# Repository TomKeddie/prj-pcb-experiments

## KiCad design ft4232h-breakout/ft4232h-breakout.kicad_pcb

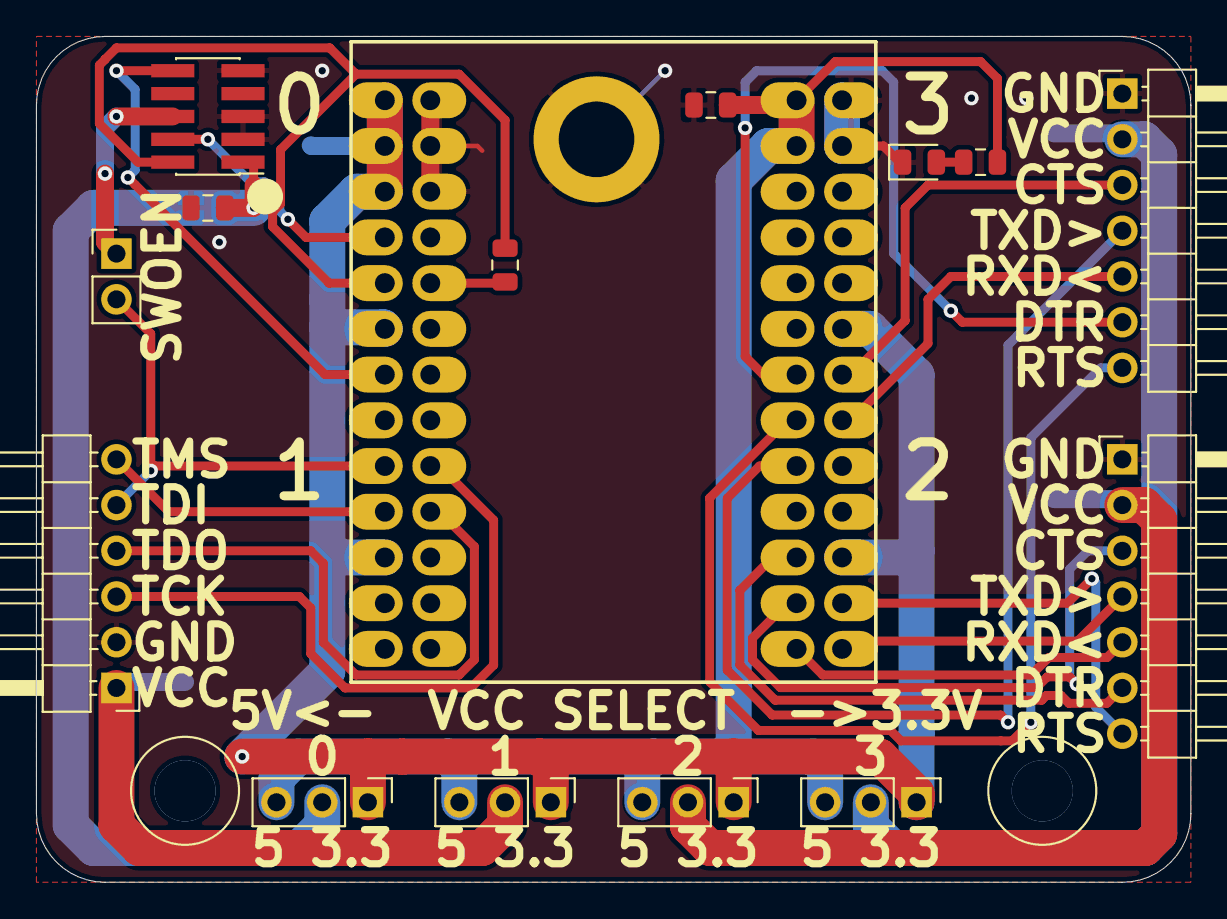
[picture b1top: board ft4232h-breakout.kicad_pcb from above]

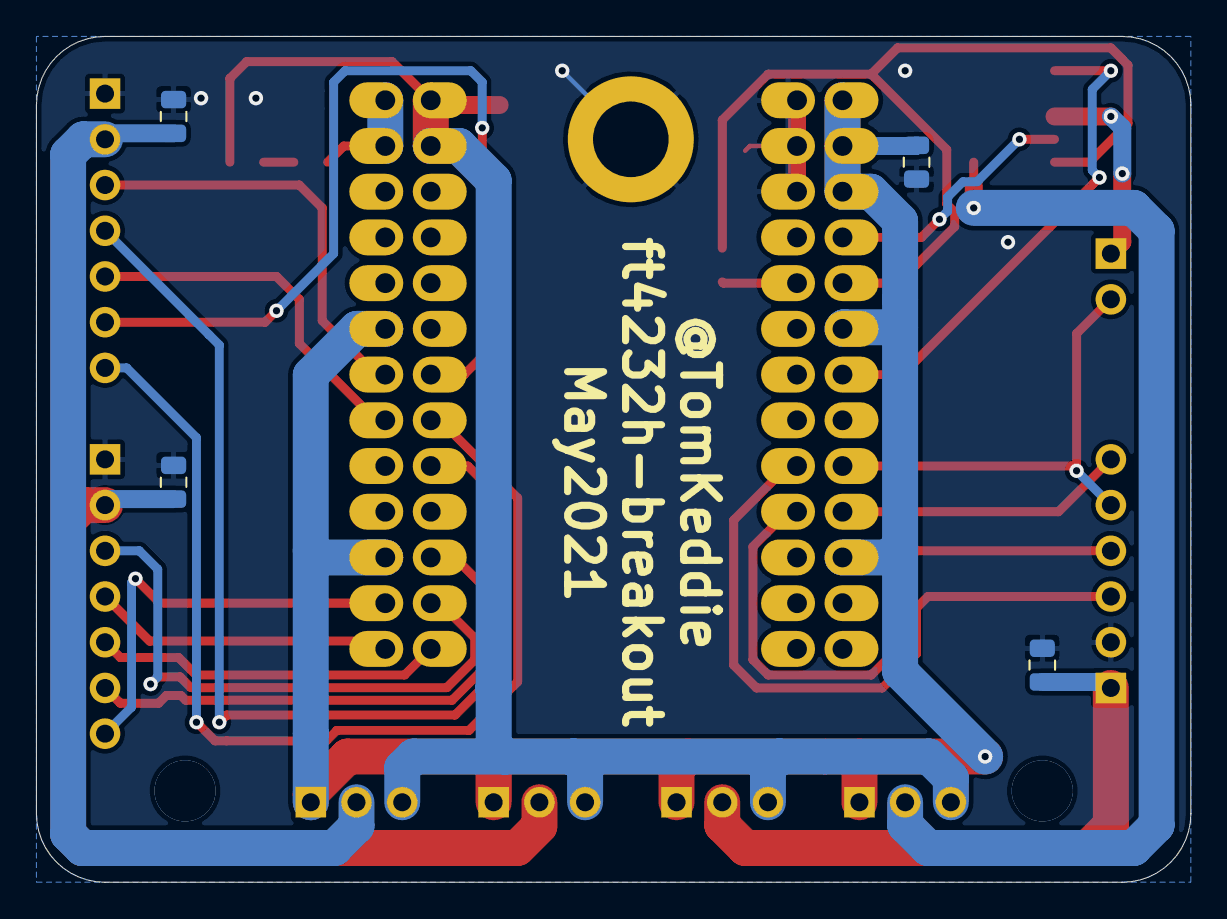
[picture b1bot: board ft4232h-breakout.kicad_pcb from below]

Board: 2 copper layers, 64.1 x 47.0 mm, 20 parts (5 on the bottom side), 27 nets.

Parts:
C1, C2, C3, C4, C5, C6: 10uF/10V; C_0805_2012Metric
D1: LED; LED_0805_2012Metric
J1, J2, J3, J4: Conn_01x03; PinHeader_1x03_P2.54mm_Vertical
J5: Conn_02x05_SWD; PinHeader_2x05_P1.27mm_Vertical_SMD
J6, J7: Conn_01x07; PinHeader_1x07_P2.54mm_Horizontal
J8: Conn_01x06; PinHeader_1x06_P2.54mm_Horizontal
J9: Conn_01x02; PinHeader_1x02_P2.54mm_Vertical
R1: 330R; R_0805_2012Metric
R2: 1k; R_0805_2012Metric
TP1: TestPoint; STUD_SOLDER_SMTSO_M3
X1: FT4232H-MODULE

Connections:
+3V3: C2.1, J1.1, J2.1, J3.1, J4.1, X1.2-1, X1.2-3, X1.2-5, X1.2-11, X1.2-21, X1.3-12, X1.3-22
+5V: C1.2, J1.3, J2.3, J3.3, J4.3, R2.1, X1.3-1, X1.3-3
/CTS-C: J7.3, X1.3-23
/CTS-D: J6.3, X1.3-14
/DTR-C: J7.6, X1.3-21
/DTR-D: J6.6, X1.3-13
/RST-A: J5.10, X1.2-13
/RTS-C: J7.7, X1.3-24
/RTS-D: J6.7, X1.3-15
/RXD-C: J7.5, X1.3-25
/RXD-D: J6.5, X1.3-16
/SWO: J5.6, J9.1
/TCK-A: J5.4, X1.2-7
/TCK-B: J8.3, X1.2-18
/TDI-A: R1.1, X1.2-10
/TDI-B: J8.5, J9.2, X1.2-17
/TDO-A: J5.2, R1.2, X1.2-9
/TDO-B: J8.4, X1.2-20
/TMS-B: J8.6, X1.2-19
/TXD-C: J7.4, X1.3-26
/TXD-D: J6.4, X1.3-17
/VCC-A: C5.1, J4.2, J5.1
/VCC-B: C4.1, J3.2, J8.1
/VCC-C: C3.1, J2.2, J7.2
/VCC-D: C6.1, J1.2, J6.2
GND: C1.1, C2.2, C3.2, C4.2, C5.2, C6.2, D1.1, J5.3, J5.5, J5.9, J6.1, J7.1, J8.2, TP1.1, X1.2-2, X1.2-4, X1.2-6, X1.3-2, X1.3-4
unnamed: D1.2, R2.2

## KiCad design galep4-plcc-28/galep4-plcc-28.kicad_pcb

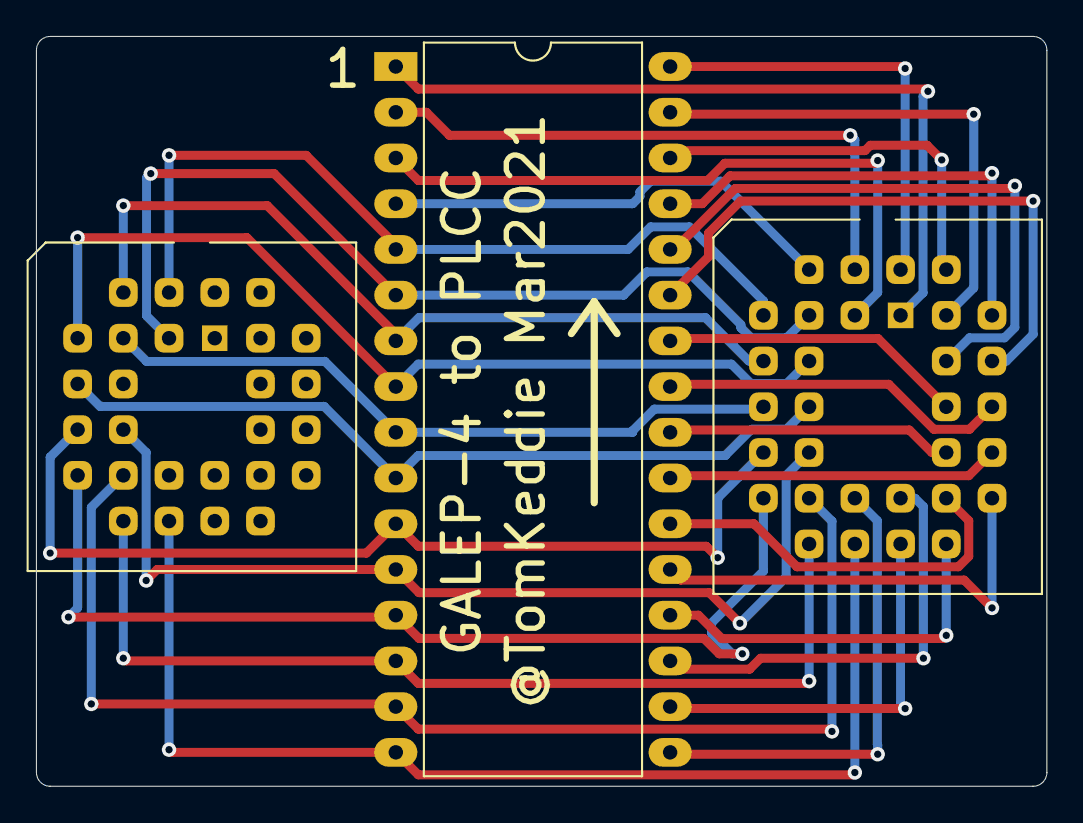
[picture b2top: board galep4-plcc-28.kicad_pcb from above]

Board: 2 copper layers, 56.1 x 41.7 mm, 3 parts (0 on the bottom side), 32 nets.

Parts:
U1: GAL22V10PLCC; PLCC-28_THT-Socket
U2: 27C040; PLCC-32_THT-Socket
U3: DIP_32; DIP-32_W15.24mm_LongPads

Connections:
/1: U2.1, U3.1
/2: U2.2, U3.2
/3: U2.3, U3.3
/4: U2.4, U3.4
/10: U1.7, U2.10, U3.10
/11: U1.9, U2.11, U3.11
/12: U1.10, U2.12, U3.12
/13: U1.11, U2.13, U3.13
/14: U1.12, U2.14, U3.14
/15: U1.13, U2.15, U3.15
/16: U1.14, U2.16, U3.16
/17: U2.17, U3.17
/18: U2.18, U3.18
/19: U2.19, U3.19
/20: U2.20, U3.20
/21: U2.21, U3.21
/22: U2.22, U3.22
/23: U2.23, U3.23
/24: U2.24, U3.24
/24-1: U1.2, U2.5, U3.5
/24-2: U1.3, U2.6, U3.6
/24-3: U1.4, U2.7, U3.7
/24-4: U1.5, U2.8, U3.8
/24-5: U1.6, U2.9, U3.9
/25: U2.25, U3.25
/26: U2.26, U3.26
/27: U2.27, U3.27
/28: U2.28, U3.28
/29: U2.29, U3.29
/30: U2.30, U3.30
/31: U2.31, U3.31
/32: U2.32, U3.32

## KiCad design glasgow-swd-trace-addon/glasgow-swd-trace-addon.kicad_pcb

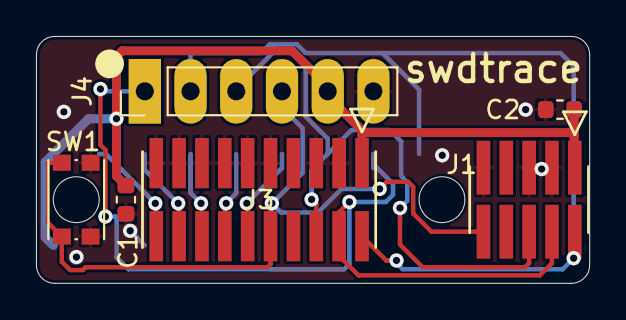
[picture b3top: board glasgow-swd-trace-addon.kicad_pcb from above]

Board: 2 copper layers, 30.7 x 13.7 mm, 7 parts (1 on the bottom side), 11 nets.

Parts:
C1, C2: 10uF/16V; R_0603_1608Metric
J1: 10pin; FTSH-105-01-F-DV-K
J2: Glasgow; 91618-310ALF
J3: 20pin; FTSH-110-01-F-DV-K
J4: Conn_01x06; PinHeader_1x06_P2.54mm_Vertical
SW1: SW_SPST; SW_Push_1P1T_NO_CK_KMR2

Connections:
/SWDCLK: J1.4, J2.15, J3.4, J4.1
/SWDIO: J1.2, J2.17, J3.2, J4.2
/SWO: J1.6, J2.13, J3.6, J4.3
/TRACECLK: J2.11, J3.12
/TRACEDATA[0]: J2.9, J3.14
/TRACEDATA[1]: J2.7, J3.16
/TRACEDATA[2]: J2.5, J3.18
/TRACEDATA[3]: J2.3, J3.20
/~RESET: J1.10, J3.10, J4.4, SW1.1
GND: C1.1, C2.1, J1.3, J1.5, J1.9, J2.4, J2.6, J2.8, J2.10, J2.12, J2.14, J2.16, J2.18, J3.3, J3.5, J3.9, J3.11, J3.13, J3.15, J3.17, J3.19, J4.6, SW1.2
VCC: C1.2, C2.2, J1.1, J2.1, J2.2, J3.1, J4.5

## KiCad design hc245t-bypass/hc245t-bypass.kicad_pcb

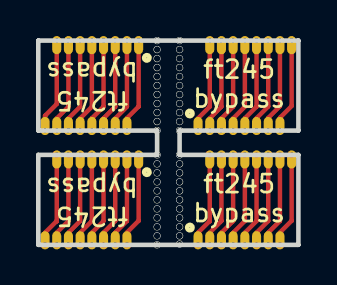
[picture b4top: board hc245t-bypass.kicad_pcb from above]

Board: 2 copper layers, 14.4 x 11.3 mm, 64 parts (0 on the bottom side), 32 nets.

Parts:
TP1, TP2, TP3, TP4, TP5, TP6, TP7, TP8, TP9, TP10, TP11, TP12, TP13, TP14, TP15, TP16, TP17, TP18, TP19, TP20, TP21, TP22, TP23, TP24, TP25, TP26, TP27, TP28, TP29, TP30, TP31, TP32, TP33, TP34, TP35, TP36, TP37, TP38, TP39, TP40, TP41, TP42, TP43, TP44, TP45, TP46, TP47, TP48, TP49, TP50, TP51, TP52, TP53, TP54, TP55, TP56, TP57, TP58, TP59, TP60, TP61, TP62, TP63, TP64: TestPoint; Castellation_5.08_2.54

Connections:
/A0B0_1: TP1.1, TP9.1
/A1B1_1: TP2.1, TP10.1
/A1B1_2: TP17.1, TP25.1
/A1B1_3: TP33.1, TP41.1
/A1B1_4: TP49.1, TP57.1
/A2B2_1: TP3.1, TP11.1
/A2B2_2: TP18.1, TP26.1
/A2B2_3: TP34.1, TP42.1
/A2B2_4: TP50.1, TP58.1
/A3B3_1: TP4.1, TP12.1
/A3B3_2: TP19.1, TP27.1
/A3B3_3: TP35.1, TP43.1
/A3B3_4: TP51.1, TP59.1
/A4B4_1: TP5.1, TP13.1
/A4B4_2: TP20.1, TP28.1
/A4B4_3: TP36.1, TP44.1
/A4B4_4: TP52.1, TP60.1
/A5B5_1: TP6.1, TP14.1
/A5B5_2: TP21.1, TP29.1
/A5B5_3: TP37.1, TP45.1
/A5B5_4: TP53.1, TP61.1
/A6B6_1: TP7.1, TP15.1
/A6B6_2: TP22.1, TP30.1
/A6B6_3: TP38.1, TP46.1
/A6B6_4: TP54.1, TP62.1
/A7B7_1: TP8.1, TP16.1
/A7B7_2: TP23.1, TP31.1
/A7B7_3: TP39.1, TP47.1
/A7B7_4: TP55.1, TP63.1
/A8B8_2: TP24.1, TP32.1
/A8B8_3: TP40.1, TP48.1
/A8B8_4: TP56.1, TP64.1

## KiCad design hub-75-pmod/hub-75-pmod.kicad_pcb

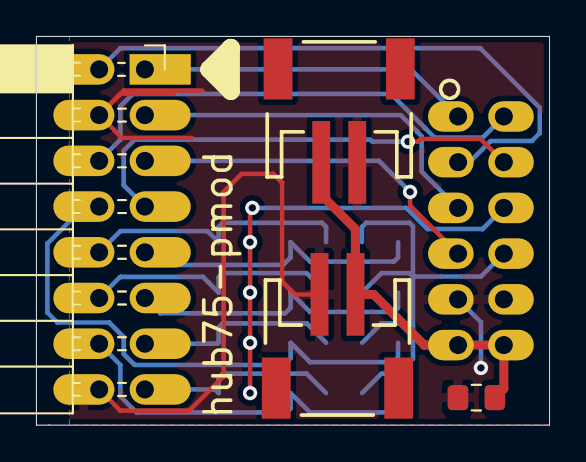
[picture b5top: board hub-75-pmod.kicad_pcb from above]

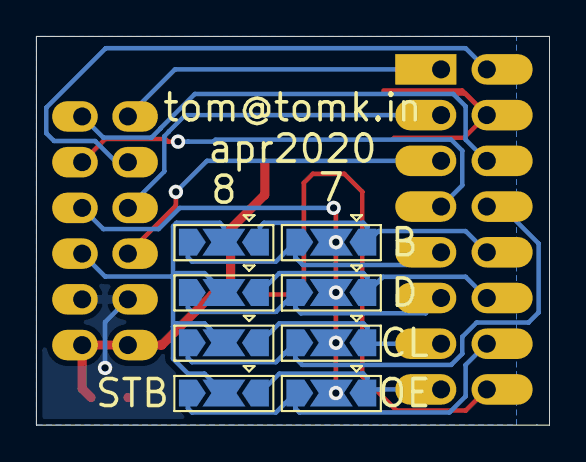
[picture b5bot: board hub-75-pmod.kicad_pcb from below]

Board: 2 copper layers, 28.5 x 21.6 mm, 13 parts (8 on the bottom side), 18 nets.

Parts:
C1: 10uF; C_0805_2012Metric_Pad1.15x1.40mm_HandSolder
J1, J4: Conn_01x02; JST-2-SMD
J2: Conn_02x08_Odd_Even; PinSocket_2x08_P2.54mm_Horizontal
J3: PMOD-2x6-FEMALE; PMOD_2X6_PTH_RA_SOCKET
JP1, JP2, JP3, JP4, JP5, JP6, JP7, JP8: JUMPER3; SolderJumper-3_P2.0mm_Open_TrianglePad1.0x1.5mm

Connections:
+3V3: C1.1, J1.1, J3.6, J3.12, J4.1
/PMOD7: J3.9, JP1.2, JP2.2, JP3.2, JP4.2
/PMOD8: J3.10, JP5.2, JP6.2, JP7.2, JP8.2
A: J2.9, JP1.3, JP5.3
B: J2.10, JP1.1, JP5.1
B0: J2.3, J3.3
B1: J2.7, J3.8
C: J2.11, JP2.3, JP6.3
CLK: J2.13, JP3.1, JP7.1
D: J2.12, JP2.1, JP6.1
E: J2.8, JP3.3, JP7.3
G0: J2.2, J3.2
G1: J2.6, J3.7
GND: C1.2, J1.2, J2.4, J2.16, J3.5, J3.11, J4.2
OE: J2.15, JP4.1, JP8.1
R0: J2.1, J3.1
R1: J2.5, J3.4
STB: J2.14, JP4.3, JP8.3

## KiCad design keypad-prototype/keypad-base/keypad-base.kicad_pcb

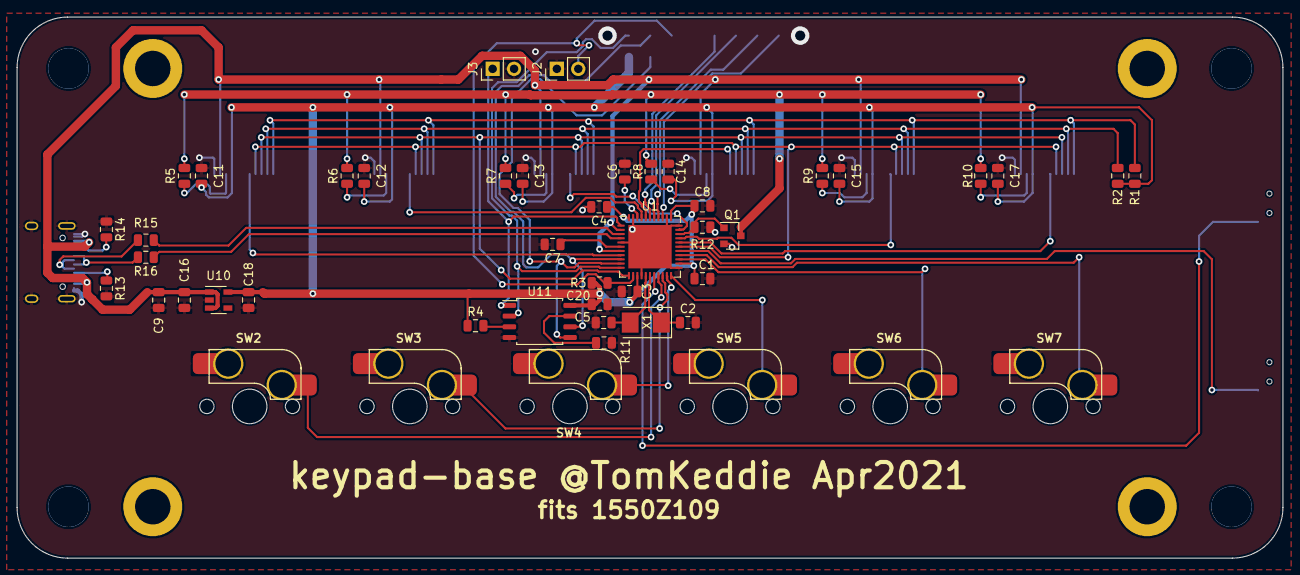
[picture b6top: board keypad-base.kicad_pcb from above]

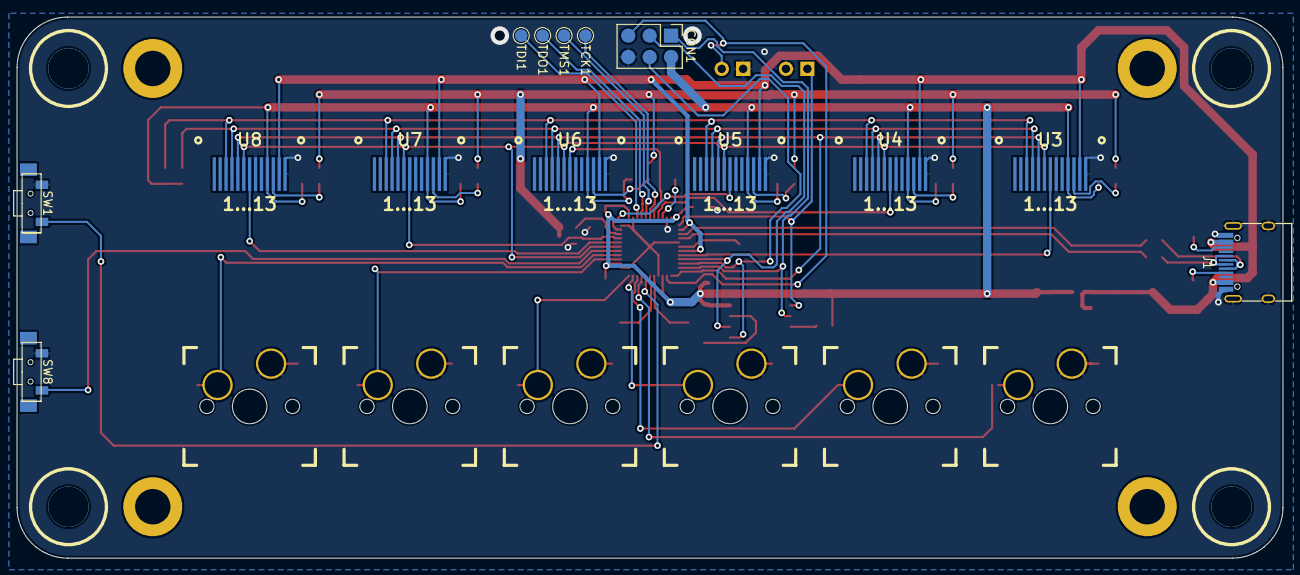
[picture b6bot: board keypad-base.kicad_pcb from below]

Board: 2 copper layers, 150.2 x 64.2 mm, 66 parts (18 on the bottom side), 50 nets.

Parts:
C1, C3, C4, C6, C8, C11, C12, C13, C14, C15, C17, C20: 0.1uF/6.3V; C_0805_2012Metric
C2, C5: 18pF; C_0805_2012Metric
C7, C16, C18: 1uF/6.3V; C_0805_2012Metric
C9: 10uF/10V; C_0805_2012Metric
CON1: AVR-ISP-6; PinTestpoint_2x03_P2.54mm_Vertical
H1: 1550Z109
H2, H3, H4, H5: mech-only-no-pins; STUD_SOLDER_SMTSO_M3
J1: USB_C_Receptacle_USB2.0; USB_C_Receptacle_GT-USB-7010
J2, J3: Conn_01x02; PinHeader_1x02_P2.54mm_Vertical
Q1: AO3400A; SOT-23
R1, R2, R3, R4, R11, R12: 10k; R_0805_2012Metric
R5, R6, R7, R8, R9, R10: 470R; R_0805_2012Metric
R13, R14: 5.1k; R_0805_2012Metric
R15, R16: 22R; R_0805_2012Metric
SW1, SW8: Switch_SW_Push; SW_SPST_SMD_SIDE_7.0x3.5
SW2, SW3, SW4, SW5, SW6, SW7: Switch_SW_Push; MX-KailhClip-1.00u-no-top-ring
TCK1: TCK; TestPoint_Pad_D1.5mm
TDI1: TDI; TestPoint_Pad_D1.5mm
TDO1: TDO; TestPoint_Pad_D1.5mm
TMS1: TMS; TestPoint_Pad_D1.5mm
U1: ATmega32U4-MU; QFN-44-1EP_7x7mm_P0.5mm_EP5.15x5.15mm
U3, U4, U5, U6, U7, U8: IE096HQ1301CL
U10: AP2112K-3.3; SOT-23-5
U11: W25Q128JVS; SOIC-8_5.23x5.23mm_P1.27mm
X1: 16MHz; Crystal_SMD_5032-2Pin_5.0x3.2mm

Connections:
+3V3: C1.1, C3.1, C4.1, C8.1, C11.1, C12.1, C13.1, C14.1, C15.1, C17.1, C18.1, C20.1, CON1.2, R1.1, R2.1, R3.1, R4.1, U1.14, U1.24, U1.34, U1.44, U3.10, U4.10, U5.10, U6.10, U7.10, U8.10, U10.5, U11.8
+5V: C9.1, C16.1, J1.A4, J1.A9, J1.B4, J1.B9, U1.2, U1.7, U3.12, U4.12, U5.12, U6.12, U7.12, U8.12, U10.1, U10.3
/AREF: C6.2, U1.42
/BACKLIGHT: Q1.1, R12.1, U1.31
/BACKLIGHTK: Q1.3, R5.2, R6.2, R7.2, R8.2, R9.2, R10.2
/CC1: J1.A5, R13.1
/CC2: J1.B5, R14.2
/D\C: U1.12, U3.5, U4.5, U5.5, U6.5, U7.5, U8.5
/D_N: J1.A7, J1.B7, R15.2
/D_P: J1.A6, J1.B6, R16.2
/MISO: CON1.1, U1.11, U11.2
/MOSI: CON1.4, U1.10, U11.5
/SCK: CON1.3, U1.9, U11.6
/SCL: R2.2, U3.4, U4.4, U5.4, U6.4, U7.4, U8.4
/SDA: R1.2, U3.3, U4.3, U5.3, U6.3, U7.3, U8.3
/SW1: SW1.2, U1.18
/SW2: SW2.2, U1.19
/SW3: SW3.2, U1.20
/SW4: SW4.2, U1.21
/SW5: SW5.2, U1.22
/SW6: SW6.2, U1.25
/SW7: SW7.2, U1.26
/SW8: SW8.2, U1.27
/TCK: TCK1.1, U1.39
/TDI: TDI1.1, U1.36
/TDO: TDO1.1, U1.37
/TMS: TMS1.1, U1.38
/UCAP: C7.1, U1.6
/USB_N: R15.1, U1.3
/USB_P: R16.1, U1.4
/XTAL1: C2.1, U1.17, X1.1
/XTAL2: C5.1, U1.16, X1.2
/~CS2: U1.8, U3.7
/~CS3: U1.41, U4.7
/~CS4: U1.40, U6.7
/~CS5: U1.32, U5.7
/~CS6: U1.30, U7.7
/~CS7: U1.29, U8.7
/~FLASH_CS: J3.1, U1.1, U11.1
/~LCDRESET: U1.28, U3.6, U4.6, U5.6, U6.6, U7.6, U8.6
/~RESET: CON1.5, J2.2, R3.2, U1.13
GND: C1.2, C2.2, C3.2, C4.2, C5.2, C6.1, C7.2, C8.2, C9.2, C11.2, C12.2, C13.2, C14.2, C15.2, C16.2, C17.2, C18.2, C20.2, CON1.6, J1.A1, J1.A12, J1.B1, J1.B12, J1.S1, J2.1, J3.2, Q1.2, R11.1, R12.2, R13.2, R14.1, SW1.1, SW2.1, SW3.1, SW4.1, SW5.1, SW6.1, SW7.1, SW8.1, U1.5, U1.15, U1.23, U1.33, U1.35, U1.43, U1.45, U3.8, U3.13, U4.8, U4.13, U5.8, U5.13, U6.8, U6.13, U7.8, U7.13, U8.8, U8.13, U10.2, U11.4
unnamed: R4.2, U11.3
unnamed: R5.1, U3.11
unnamed: R6.1, U4.11
unnamed: R7.1, U5.11
unnamed: R8.1, U6.11
unnamed: R9.1, U7.11
unnamed: R10.1, U8.11
unnamed: R11.2, U11.7

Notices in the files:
parts and their libraries:
Copyright 2016 Accelerated Designs. All rights reserved.
